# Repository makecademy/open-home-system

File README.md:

open-home-system
================

Repository for the Open Home System (OHS) modules & software. The repository is organized as following:

- Hardware: all the devices included in the Open Home System. For each device, you will find Arduino sketches (to test the module & connect it to the whole system) and 3D files for the cases.
The folder common contains the common files used for Open Home System, like the Arduino library, the primitives for the cases, and the schematic & layout for the Open Home System board.

- Software: all the software you need to run Open Home System.

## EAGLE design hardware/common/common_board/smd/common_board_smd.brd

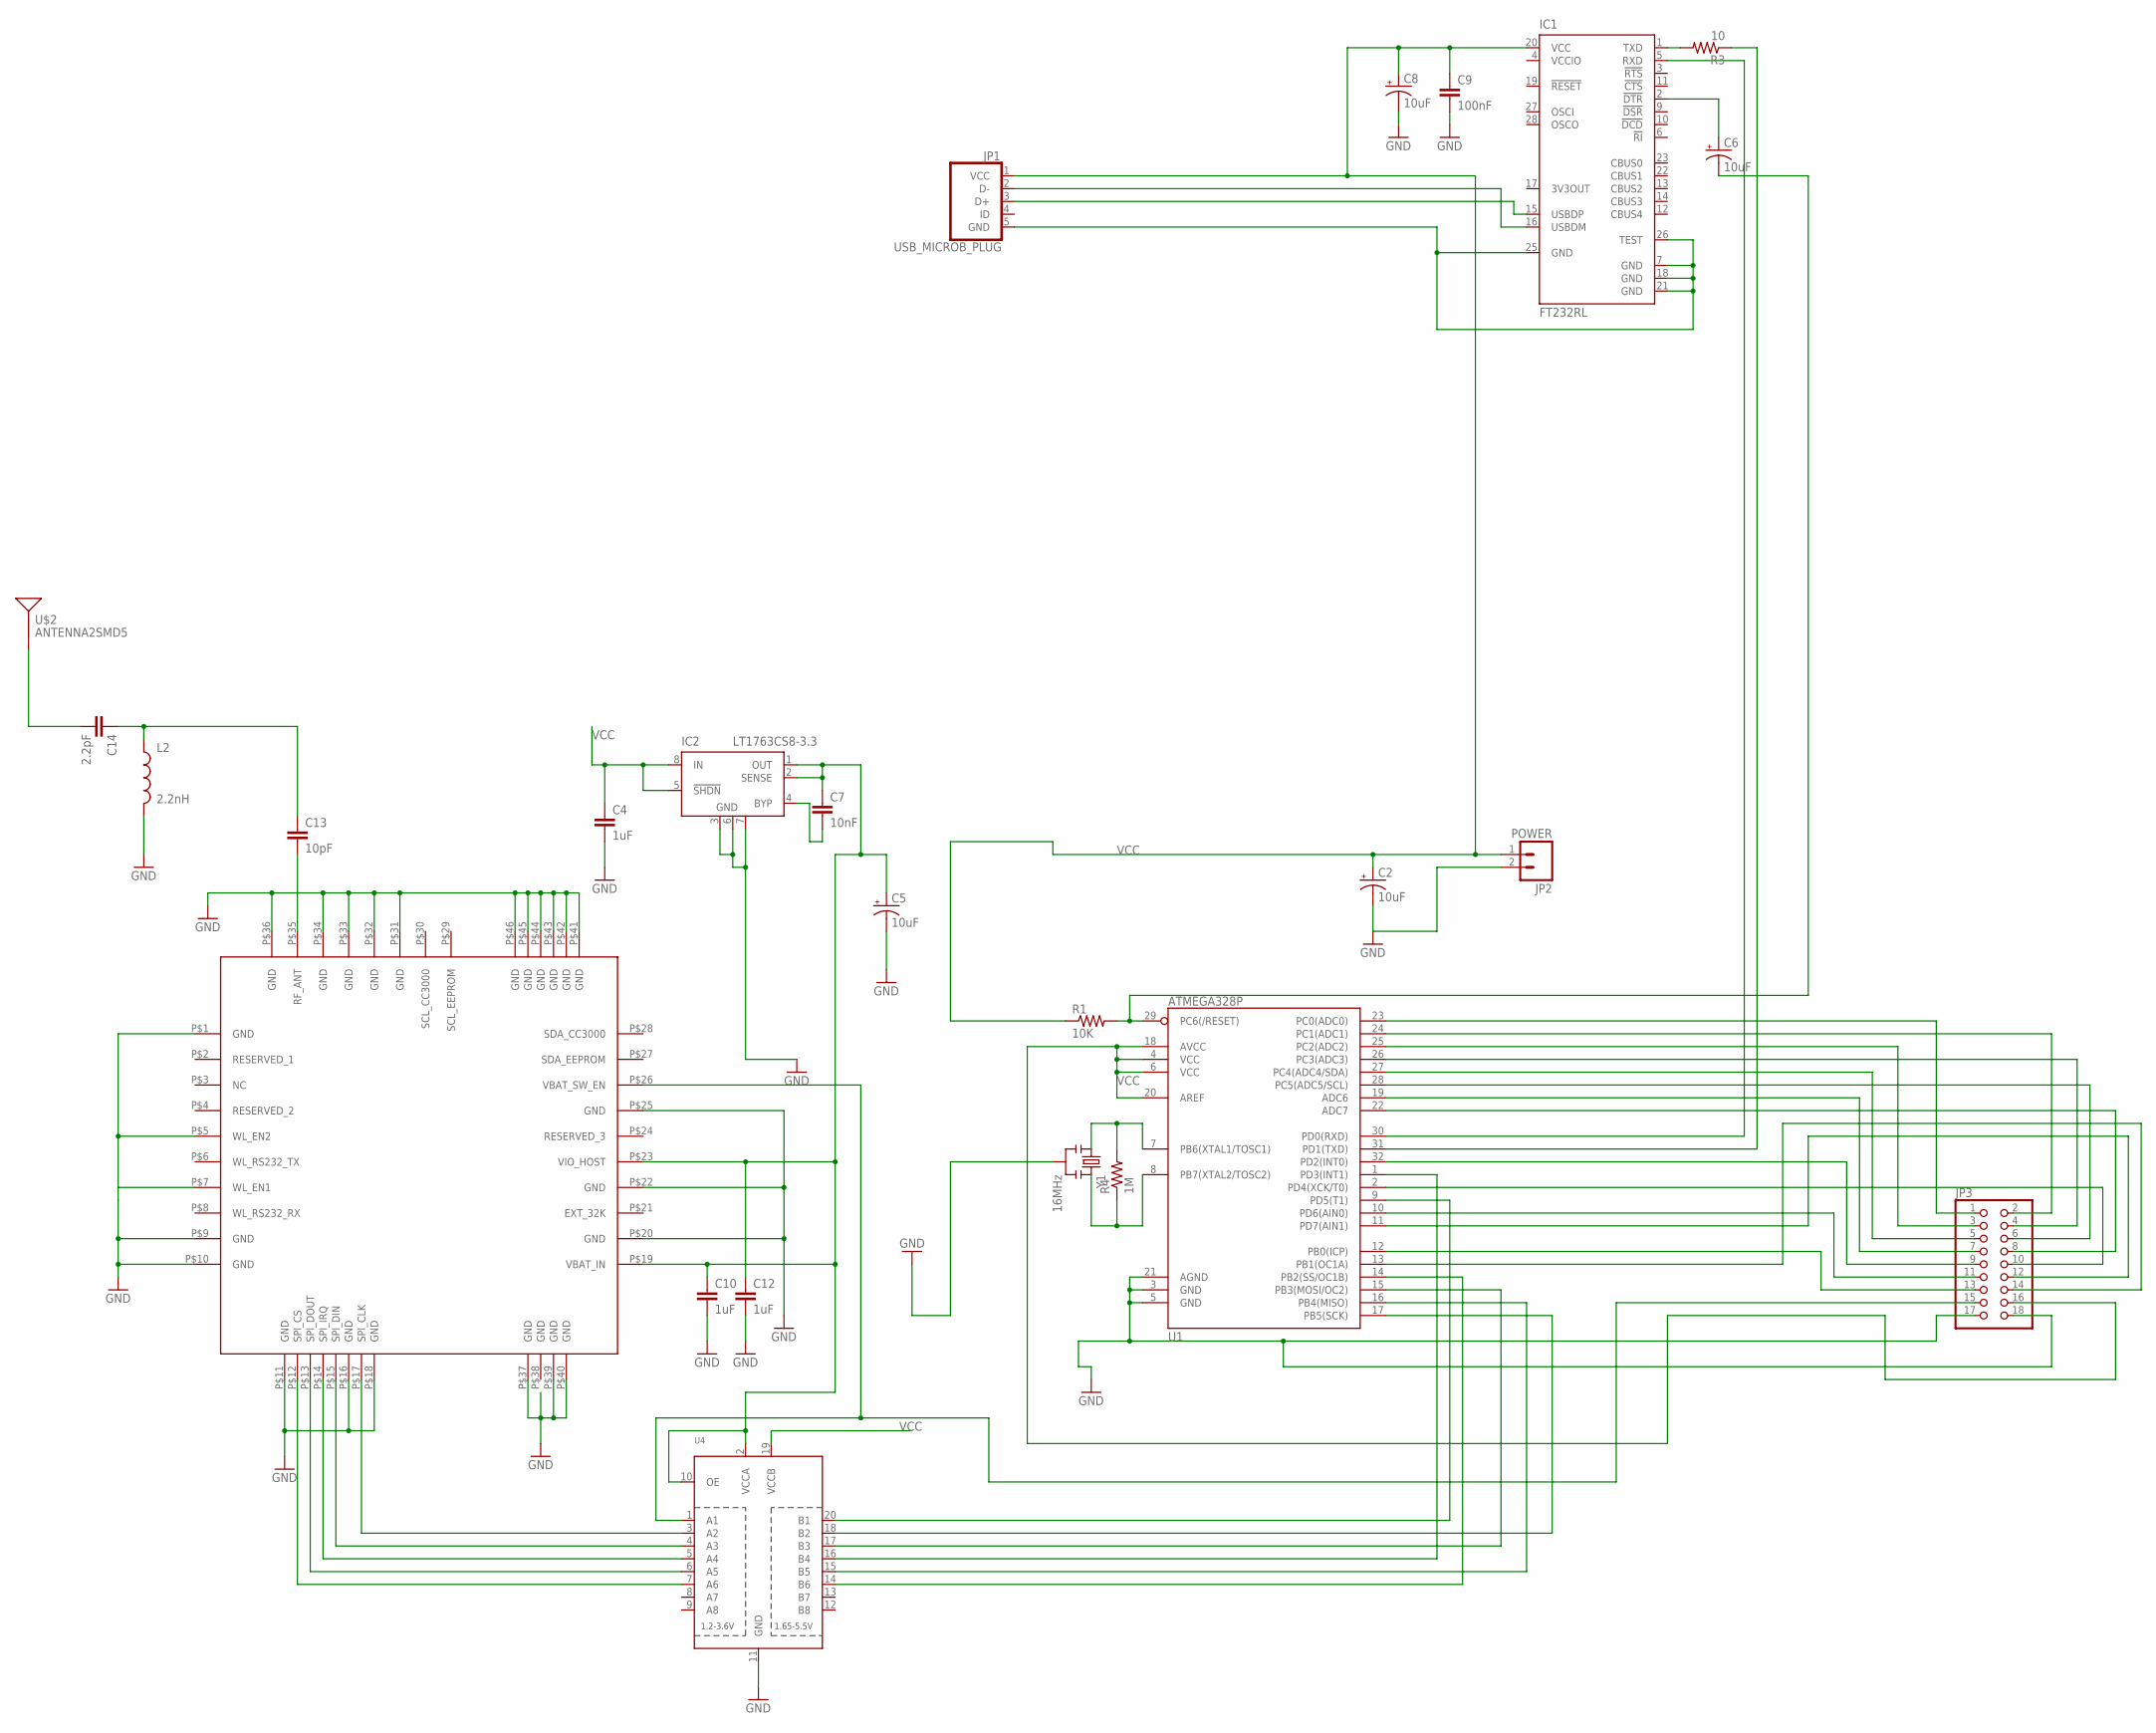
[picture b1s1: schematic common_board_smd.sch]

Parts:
C2, C6, C8: 10uF; EIA3216
C4: 1uF; 0805
C5: 10uF; EIA3528
C7: 10nF; 0805
C9: 100nF; 0805
C10, C12: 1uF; 1206
C13: 10pF; 0805
C14: 2.2pF; 0805
IC1: FT232RL; SSOP28
IC2: LT1763CS8-3.3; SOIC8
JP1: USB_MICROB_PLUG; MICRO-B-RA-SMT
JP2: POWER; 1X02
JP3: PINHD-2X9-BIG; 2X09-BIG
L2: 2.2nH; 0805
R1: 10K; 0805
R3: 10; 0805
R4: 1M; 0603-RES
U1: ATMEGA328P; TQFP32-08
U4: TXB0108PWR; TSSOP20
U$1: CC3000
U$2: ANTENNA2SMD5; ANTENNA-CHIP5
Y1: 16MHz; RESONATOR-SMD

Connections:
GND: C2.C (-), C4.2, C5.C (-), C8.C (-), C9.2, C10.2, C12.2, IC2.3 (GND), IC2.6 (GND), IC2.7 (GND), JP2.2, JP3.17, JP3.18, L2.2, U1.3 (GND), U1.5 (GND), U1.21 (AGND), U4.11 (GND), U$1.P$1 (GND), U$1.P$5 (WL_EN2), U$1.P$7 (WL_EN1), U$1.P$9 (GND), U$1.P$10 (GND), U$1.P$11 (GND), U$1.P$16 (GND), U$1.P$18 (GND), U$1.P$20 (GND), U$1.P$22 (GND), U$1.P$25 (GND), U$1.P$31 (GND), U$1.P$32 (GND), U$1.P$33 (GND), U$1.P$34 (GND), U$1.P$36 (GND), U$1.P$37 (GND), U$1.P$39 (GND), U$1.P$40 (GND), U$1.P$41 (GND), U$1.P$42 (GND), U$1.P$43 (GND), U$1.P$44 (GND), U$1.P$45 (GND), U$1.P$46 (GND), Y1.2
unnamed: U1.9 (PD5(T1)), U4.20 (B1)
unnamed: U1.1 (PD3(INT1)), U4.16 (B4)
unnamed: C6.C (-), R1.2, U1.29 (PC6(/RESET))
unnamed: R4.2, U1.7 (PB6(XTAL1/TOSC1)), Y1.1
unnamed: U1.17 (PB5(SCK)), U4.18 (B2)
unnamed: U1.14 (PB2(SS/OC1B)), U4.14 (B6)
unnamed: JP3.14, U1.13 (PB1(OC1A))
unnamed: C5.A (+), C7.1, C10.1, C12.1, IC2.1 (OUT), IC2.2 (SENSE), U4.2 (VCCA), U4.10 (OE), U$1.P$19 (VBAT_IN), U$1.P$23 (VIO_HOST)
unnamed: U4.7 (A6), U$1.P$12 (SPI_CS)
unnamed: U4.6 (A5), U$1.P$13 (SPI_DOUT)
unnamed: U4.5 (A4), U$1.P$14 (SPI_IRQ)
unnamed: U4.4 (A3), U$1.P$15 (SPI_DIN)
unnamed: U4.3 (A2), U$1.P$17 (SPI_CLK)
unnamed: JP3.15, U4.1 (A1), U$1.P$26 (VBAT_SW_EN)
unnamed: IC1.1 (TXD), R3.2
unnamed: C13.2, U$1.P$35 (RF_ANT)
unnamed: C13.1, C14.1, L2.1
unnamed: C14.2, U$2.FEED
unnamed: U1.16 (PB4(MISO)), U4.15 (B5)
unnamed: U1.15 (PB3(MOSI/OC2)), U4.17 (B3)
unnamed: JP3.9, U1.32 (PD2(INT0))
unnamed: JP3.13, U1.12 (PB0(ICP))
unnamed: JP3.3, U1.25 (PC2(ADC2))
unnamed: JP3.8, U1.22 (ADC7)
unnamed: JP3.1, U1.23 (PC0(ADC0))
unnamed: JP3.12, U1.11 (PD7(AIN1))
unnamed: JP3.2, U1.24 (PC1(ADC1))
unnamed: IC1.15 (USBDP), JP1.3 (D+)
unnamed: IC1.16 (USBDM), JP1.2 (D-)
unnamed: R3.1, U1.31 (PD1(TXD))
unnamed: IC1.5 (RXD), U1.30 (PD0(RXD))
unnamed: C6.A (+), IC1.2 (!DTR)
unnamed: JP3.4, U1.26 (PC3(ADC3))
unnamed: JP3.5, U1.27 (PC4(ADC4/SDA))
unnamed: JP3.6, U1.28 (PC5(ADC5/SCL))
unnamed: JP3.7, U1.19 (ADC6)
unnamed: JP3.10, U1.2 (PD4(XCK/T0))
unnamed: IC1.7 (GND), IC1.18 (GND), IC1.21 (GND), IC1.25 (GND), IC1.26 (TEST), JP1.5 (GND)
unnamed: R4.1, U1.8 (PB7(XTAL2/TOSC2)), Y1.3
unnamed: C7.2, IC2.4 (BYP)
unnamed: JP3.11, U1.10 (PD6(AIN0))
SCL_CC3000: U$1.P$30 (SCL_CC3000)
SCL_EEPROM: U$1.P$29 (SCL_EEPROM)
VCC: C2.A (+), C4.1, C8.A (+), C9.1, IC1.20 (VCC), IC2.5 (!SHDN), IC2.8 (IN), JP1.1 (VCC), JP2.1, JP3.16, R1.1, U1.4 (VCC), U1.6 (VCC), U1.18 (AVCC), U1.20 (AREF), U4.19 (VCCB)
VCCIO: IC1.4 (VCCIO)

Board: 2 copper layers, 25 parts (0 on the bottom side), 43 nets, no tracks yet.

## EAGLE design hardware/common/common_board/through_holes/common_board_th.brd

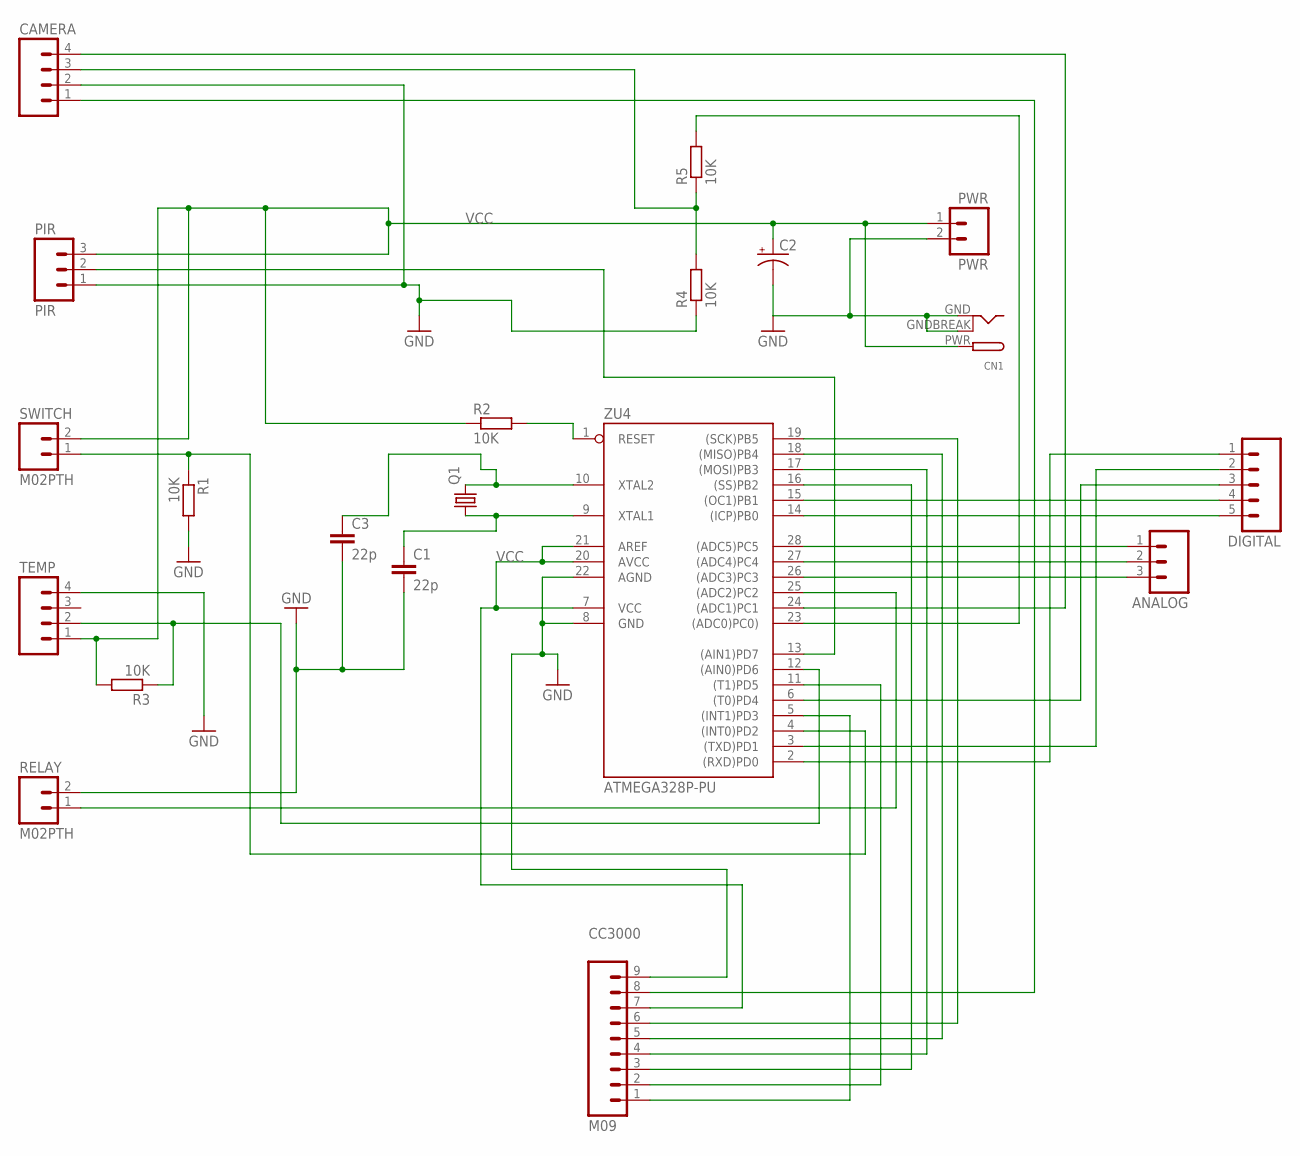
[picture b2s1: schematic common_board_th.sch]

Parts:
ANALOG: M03PTH; 1X03
C1, C3: 22p; C050-025X075
C2: CAP_POLPTH1; CPOL-RADIAL-100UF-25V
CAMERA: M04PTH; 1X04
CC3000: M09; 1X09
CN1: DCBARRELPTH; DCJACK_2MM_PTH
DIGITAL: M05PTH; 1X05
PIR: PIR; 1X03
PWR: PWR; 1X02
Q1: CRYSTALHC49S; HC49/S
R1, R2, R3, R4, R5: 10K; 0207/7
RELAY: M02PTH; 1X02
SWITCH: M02PTH; 1X02
TEMP: M04PTH; 1X04
ZU4: ATMEGA328P-PU; DIL28-3

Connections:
GND: C1.2, C2.2 (-), C3.2, CAMERA.2, CC3000.9, CN1.GND, CN1.GNDBREAK, PIR.1, PWR.2, R1.2, R4.1, RELAY.2, TEMP.4, ZU4.8 (GND), ZU4.22 (AGND)
unnamed: CC3000.2, ZU4.11 ((T1)PD5)
unnamed: CC3000.1, ZU4.5 ((INT1)PD3)
unnamed: R2.2, ZU4.1 (RESET)
unnamed: C1.1, Q1.1, ZU4.9 (XTAL1)
unnamed: CC3000.6, ZU4.19 ((SCK)PB5)
unnamed: CC3000.3, ZU4.16 ((SS)PB2)
unnamed: R1.1, SWITCH.1, ZU4.4 ((INT0)PD2)
unnamed: RELAY.1, ZU4.25 ((ADC2)PC2)
unnamed: R3.1, TEMP.2, ZU4.12 ((AIN0)PD6)
unnamed: ANALOG.1, ZU4.28 ((ADC5)PC5)
unnamed: CAMERA.1, CC3000.8
unnamed: CAMERA.4, ZU4.24 ((ADC1)PC1)
unnamed: CAMERA.3, R4.2, R5.1
unnamed: ANALOG.2, ZU4.27 ((ADC4)PC4)
unnamed: R5.2, ZU4.23 ((ADC0)PC0))
unnamed: ANALOG.3, ZU4.26 ((ADC3)PC3)
unnamed: DIGITAL.4, ZU4.15 ((OC1)PB1)
unnamed: DIGITAL.5, ZU4.14 ((ICP)PB0)
unnamed: CC3000.5, ZU4.18 ((MISO)PB4)
unnamed: CC3000.4, ZU4.17 ((MOSI)PB3)
unnamed: DIGITAL.3, ZU4.6 ((T0)PD4)
unnamed: DIGITAL.2, ZU4.3 ((TXD)PD1)
unnamed: DIGITAL.1, ZU4.2 ((RXD)PD0)
unnamed: PIR.2, ZU4.13 ((AIN1)PD7)
VCC: C2.1 (+), CC3000.7, CN1.PWR, PIR.3, PWR.1, R2.1, R3.2, SWITCH.2, TEMP.1, ZU4.7 (VCC), ZU4.20 (AVCC), ZU4.21 (AREF)
XTAL2: C3.1, Q1.2, ZU4.10 (XTAL2)

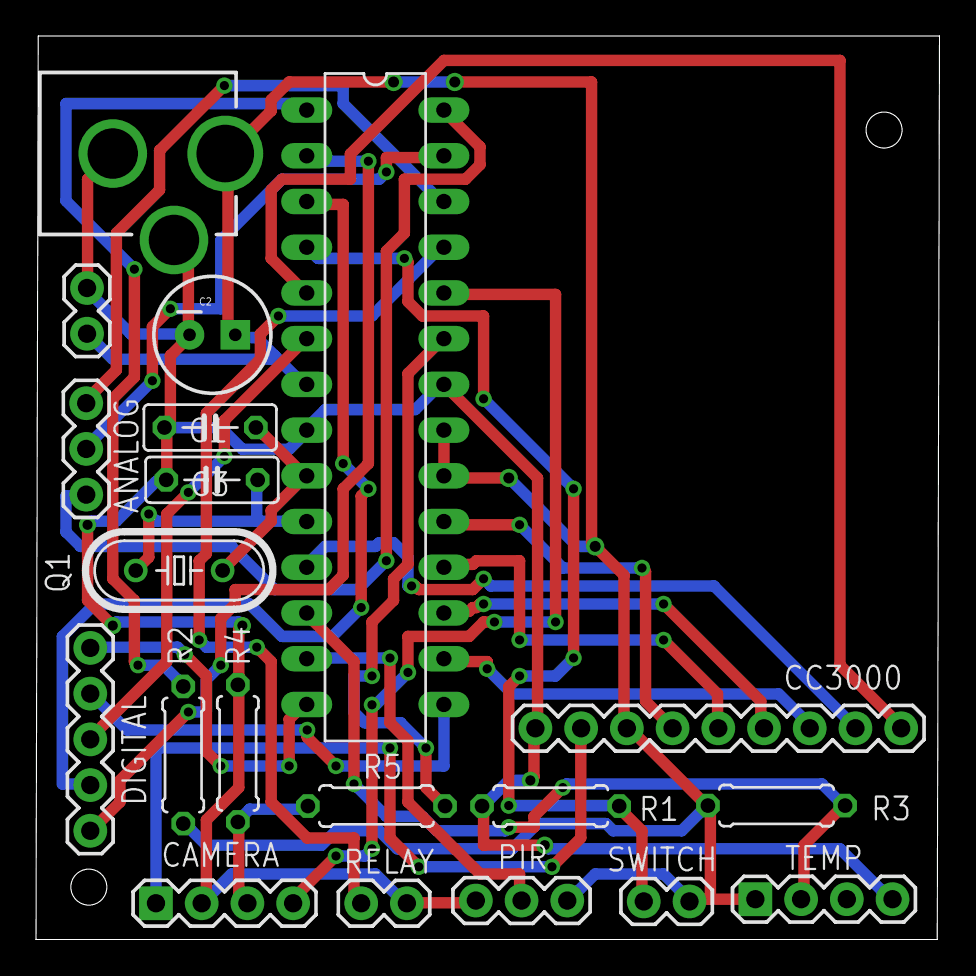
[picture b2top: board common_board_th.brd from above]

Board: 2 copper layers, 50.2 x 50.2 mm, 20 parts (0 on the bottom side), 27 nets.

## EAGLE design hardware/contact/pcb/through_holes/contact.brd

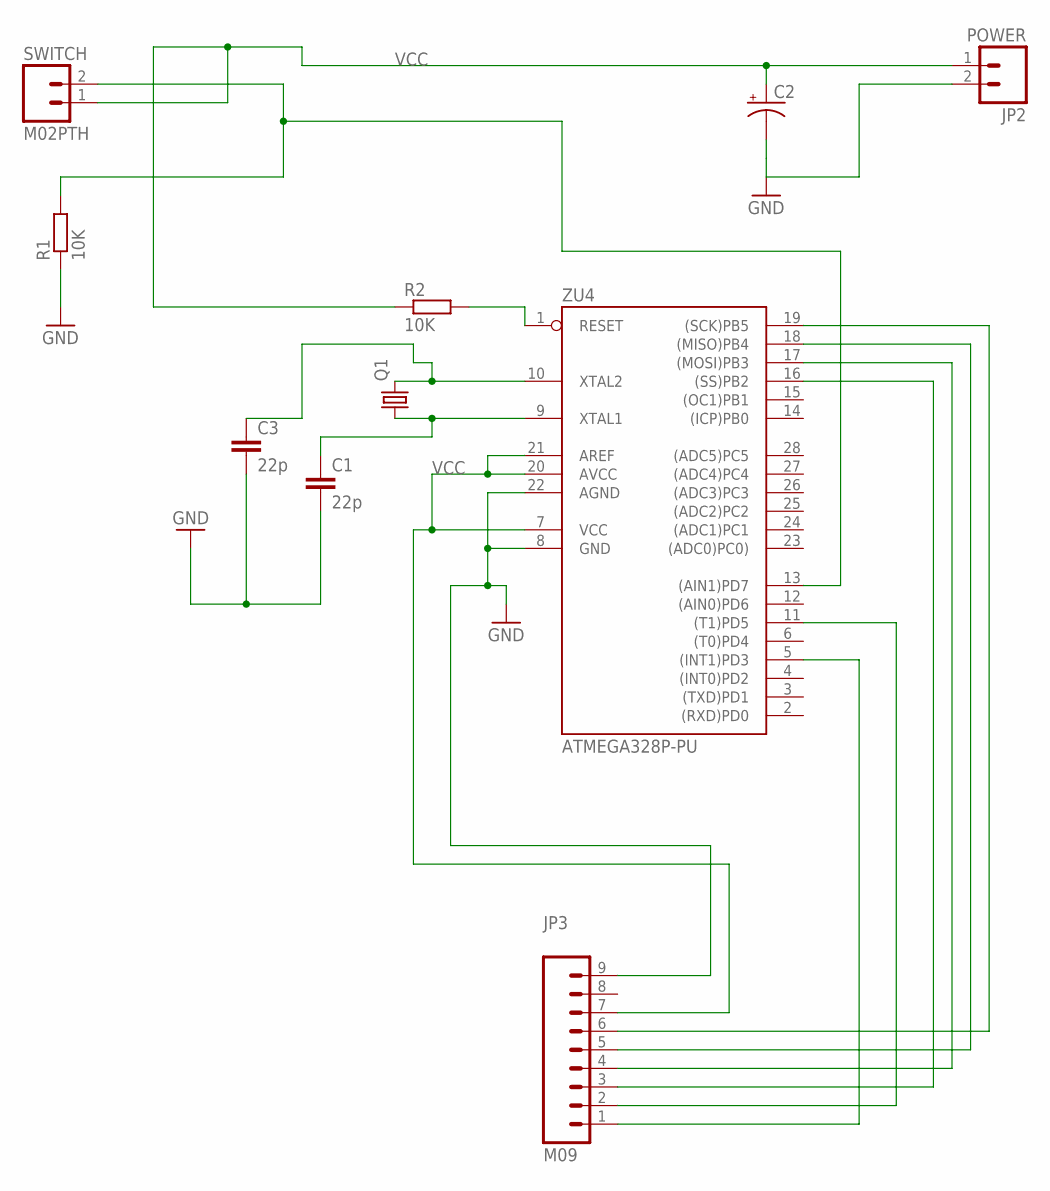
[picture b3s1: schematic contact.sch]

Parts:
C1, C3: 22p; C050-025X075
C2: CAP_POLPTH1; CPOL-RADIAL-100UF-25V
JP2: POWER; 1X02
JP3: M09; 1X09
Q1: CRYSTALHC49S; HC49/S
R1, R2: 10K; 0207/7
SWITCH: M02PTH; 1X02
ZU4: ATMEGA328P-PU; DIL28-3

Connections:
GND: C1.2, C2.2 (-), C3.2, JP2.2, JP3.9, R1.1, ZU4.8 (GND), ZU4.22 (AGND)
unnamed: JP3.2, ZU4.11 ((T1)PD5)
unnamed: JP3.1, ZU4.5 ((INT1)PD3)
unnamed: R2.2, ZU4.1 (RESET)
unnamed: C1.1, Q1.1, ZU4.9 (XTAL1)
unnamed: JP3.6, ZU4.19 ((SCK)PB5)
unnamed: JP3.3, ZU4.16 ((SS)PB2)
unnamed: JP3.5, ZU4.18 ((MISO)PB4)
unnamed: JP3.4, ZU4.17 ((MOSI)PB3)
unnamed: R1.2, SWITCH.2, ZU4.13 ((AIN1)PD7)
VCC: C2.1 (+), JP2.1, JP3.7, R2.1, SWITCH.1, ZU4.7 (VCC), ZU4.20 (AVCC), ZU4.21 (AREF)
XTAL2: C3.1, Q1.2, ZU4.10 (XTAL2)

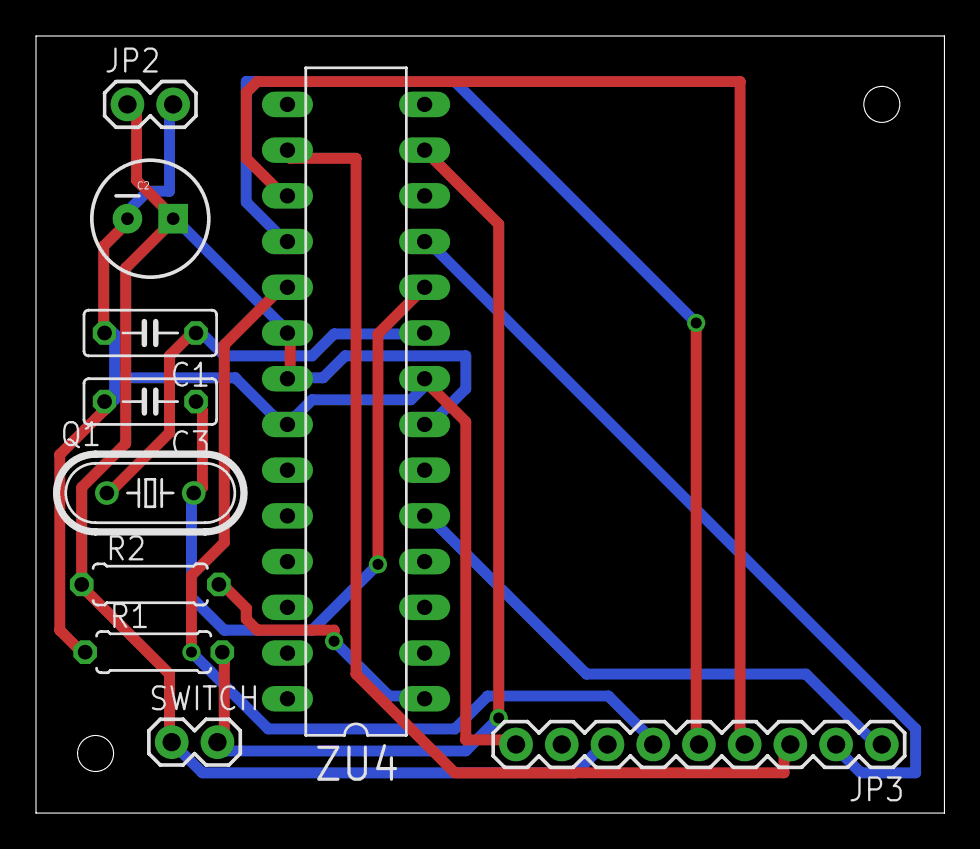
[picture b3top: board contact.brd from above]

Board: 2 copper layers, 50.5 x 43.2 mm, 10 parts (0 on the bottom side), 12 nets.

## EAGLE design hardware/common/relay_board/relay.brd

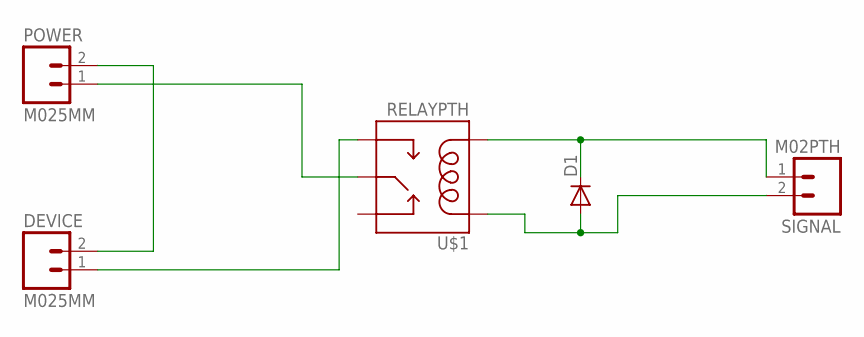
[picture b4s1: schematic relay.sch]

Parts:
D1: DIODE1N4148; DIODE-1N4148
DEVICE: M025MM; SCREWTERMINAL-5MM-2
POWER: M025MM; SCREWTERMINAL-5MM-2
SIGNAL: M02PTH; 1X02
U$1: RELAYPTH; RELAY-G5Q

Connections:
unnamed: D1.C, SIGNAL.1, U$1.1 (COIL2)
unnamed: D1.A, SIGNAL.2, U$1.5 (COIL1)
unnamed: POWER.1, U$1.2 (MAIN)
unnamed: DEVICE.1, U$1.3 (NO)
unnamed: DEVICE.2, POWER.2

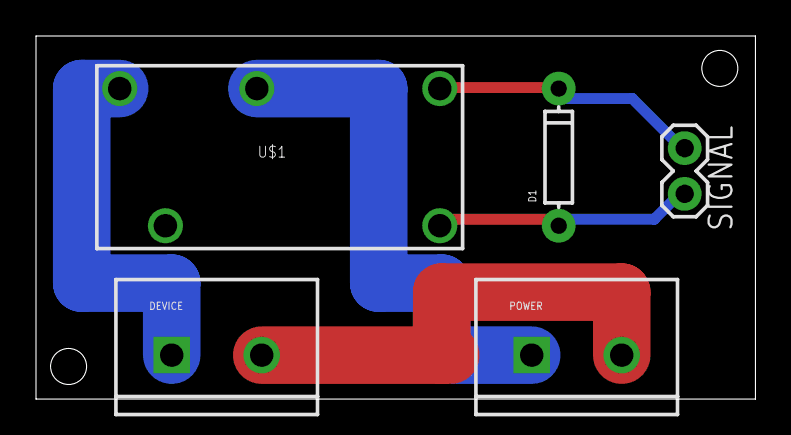
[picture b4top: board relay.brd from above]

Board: 2 copper layers, 40.0 x 20.2 mm, 5 parts (0 on the bottom side), 5 nets.

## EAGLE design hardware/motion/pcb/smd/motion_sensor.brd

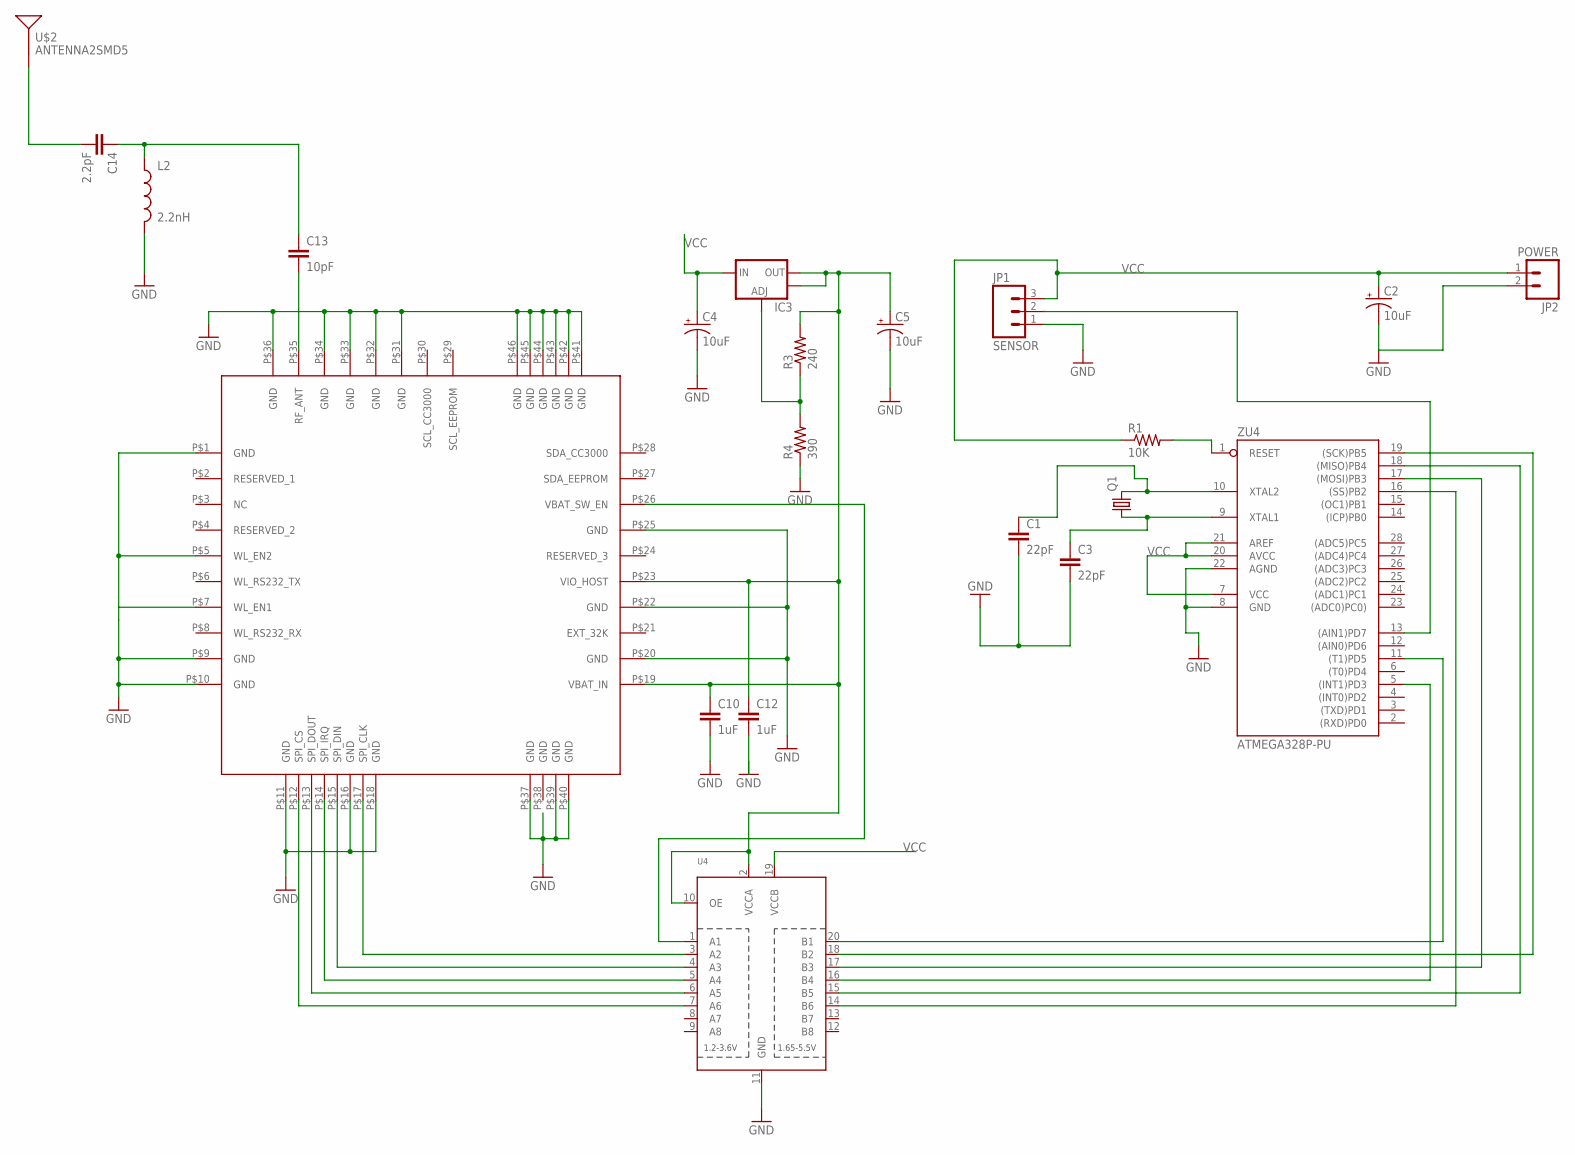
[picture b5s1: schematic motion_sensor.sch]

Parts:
C1, C3: 22pF; 0805
C2: 10uF; EIA3216
C4, C5: 10uF; EIA3528
C10, C12: 1uF; 1206
C13: 10pF; 0805
C14: 2.2pF; 0805
IC3: V_REG_LM1117SOT223; SOT223
JP1: SENSOR; 1X03
JP2: POWER; 1X02
L2: 2.2nH; 0805
Q1: CRYSTALHC49U-V; HC49U-V
R1: 10K; 0805
R3: 240; 0805
R4: 390; 0805
U4: TXB0108PWR; TSSOP20
U$1: CC3000
U$2: ANTENNA2SMD5; ANTENNA-CHIP5
ZU4: ATMEGA328P-PU; DIL28-3

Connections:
GND: C1.2, C2.C (-), C3.2, C4.C (-), C5.C (-), C10.2, JP1.1, JP2.2, L2.2, R4.1, U4.11 (GND), U$1.P$1 (GND), U$1.P$5 (WL_EN2), U$1.P$7 (WL_EN1), U$1.P$9 (GND), U$1.P$10 (GND), U$1.P$11 (GND), U$1.P$16 (GND), U$1.P$18 (GND), U$1.P$20 (GND), U$1.P$22 (GND), U$1.P$25 (GND), U$1.P$31 (GND), U$1.P$32 (GND), U$1.P$33 (GND), U$1.P$34 (GND), U$1.P$36 (GND), U$1.P$37 (GND), U$1.P$39 (GND), U$1.P$40 (GND), U$1.P$41 (GND), U$1.P$42 (GND), U$1.P$43 (GND), U$1.P$44 (GND), U$1.P$45 (GND), U$1.P$46 (GND), ZU4.8 (GND), ZU4.22 (AGND)
unnamed: U4.20 (B1), ZU4.11 ((T1)PD5)
unnamed: U4.16 (B4), ZU4.5 ((INT1)PD3)
unnamed: R1.2, ZU4.1 (RESET)
unnamed: C3.1, Q1.1, ZU4.9 (XTAL1)
unnamed: U4.18 (B2), ZU4.19 ((SCK)PB5)
unnamed: U4.14 (B6), ZU4.16 ((SS)PB2)
unnamed: C5.A (+), C10.1, C12.1, IC3.2 (OUT), IC3.4 (OUT), R3.2, U4.2 (VCCA), U4.10 (OE), U$1.P$19 (VBAT_IN), U$1.P$23 (VIO_HOST)
unnamed: U4.7 (A6), U$1.P$12 (SPI_CS)
unnamed: U4.6 (A5), U$1.P$13 (SPI_DOUT)
unnamed: U4.5 (A4), U$1.P$14 (SPI_IRQ)
unnamed: U4.4 (A3), U$1.P$15 (SPI_DIN)
unnamed: U4.3 (A2), U$1.P$17 (SPI_CLK)
unnamed: U4.1 (A1), U$1.P$26 (VBAT_SW_EN)
unnamed: IC3.1 (ADJ), R3.1, R4.2
unnamed: C13.2, U$1.P$35 (RF_ANT)
unnamed: C13.1, C14.1, L2.1
unnamed: C14.2, U$2.FEED
unnamed: U4.15 (B5), ZU4.18 ((MISO)PB4)
unnamed: U4.17 (B3), ZU4.17 ((MOSI)PB3)
unnamed: JP1.2, ZU4.13 ((AIN1)PD7)
SCL_CC3000: U$1.P$30 (SCL_CC3000)
SCL_EEPROM: U$1.P$29 (SCL_EEPROM)
VCC: C2.A (+), C4.A (+), IC3.3 (IN), JP1.3, JP2.1, R1.1, U4.19 (VCCB), ZU4.7 (VCC), ZU4.20 (AVCC), ZU4.21 (AREF)
XTAL2: C1.1, Q1.2, ZU4.10 (XTAL2)

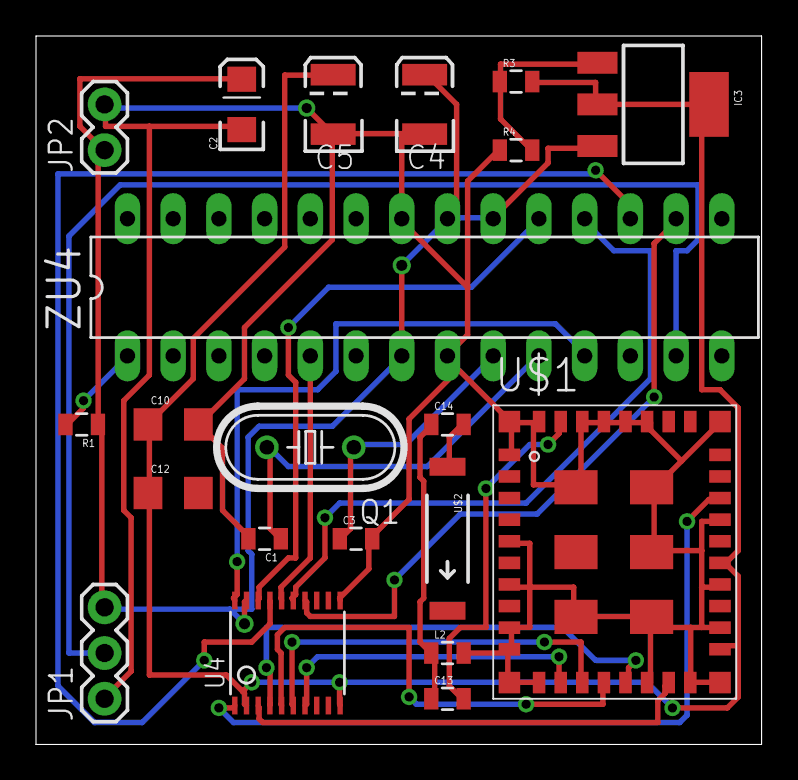
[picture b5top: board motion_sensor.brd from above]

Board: 2 copper layers, 40.3 x 39.4 mm, 21 parts (0 on the bottom side), 23 nets.

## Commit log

2013-08-08 README modified
2013-08-08 3d render of motion sensor
2013-08-08 base added
2013-08-08 base back modified
2013-08-09 first version temp case
2013-08-11 primitives integrated for motion sensor
2013-08-14 basic sketches motion and temp
2013-08-14 relay sketch added
2013-08-20 schematics added for all modules
2013-08-20 fixed camera module
2013-08-20 update camera schematics
2013-08-20 motion sensor sche
2013-08-20 temperature schem
2013-08-20 schem relay
2013-08-20 base schem
2013-09-17 major update with PCBs and sketches
2013-09-17 software update
2013-09-18 fixes in relay board
2013-09-27 common board added
2013-09-27 fixes in sketches
2013-09-30 repo cleanup
2013-10-01 update smd board

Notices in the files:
parts and their libraries:
SparkFun-Capacitors: Licensing: CC v3.0 Share-Alike You are welcome to use this library for commercial purposes.
